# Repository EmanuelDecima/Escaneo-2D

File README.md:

# Escaneo-2D
Este proyecto consiste en un sistema de escaneo rotativo bidimensional diseñado para capturar puntos del contorno de un objeto y representar digitalmente una aproximación de su perímetro

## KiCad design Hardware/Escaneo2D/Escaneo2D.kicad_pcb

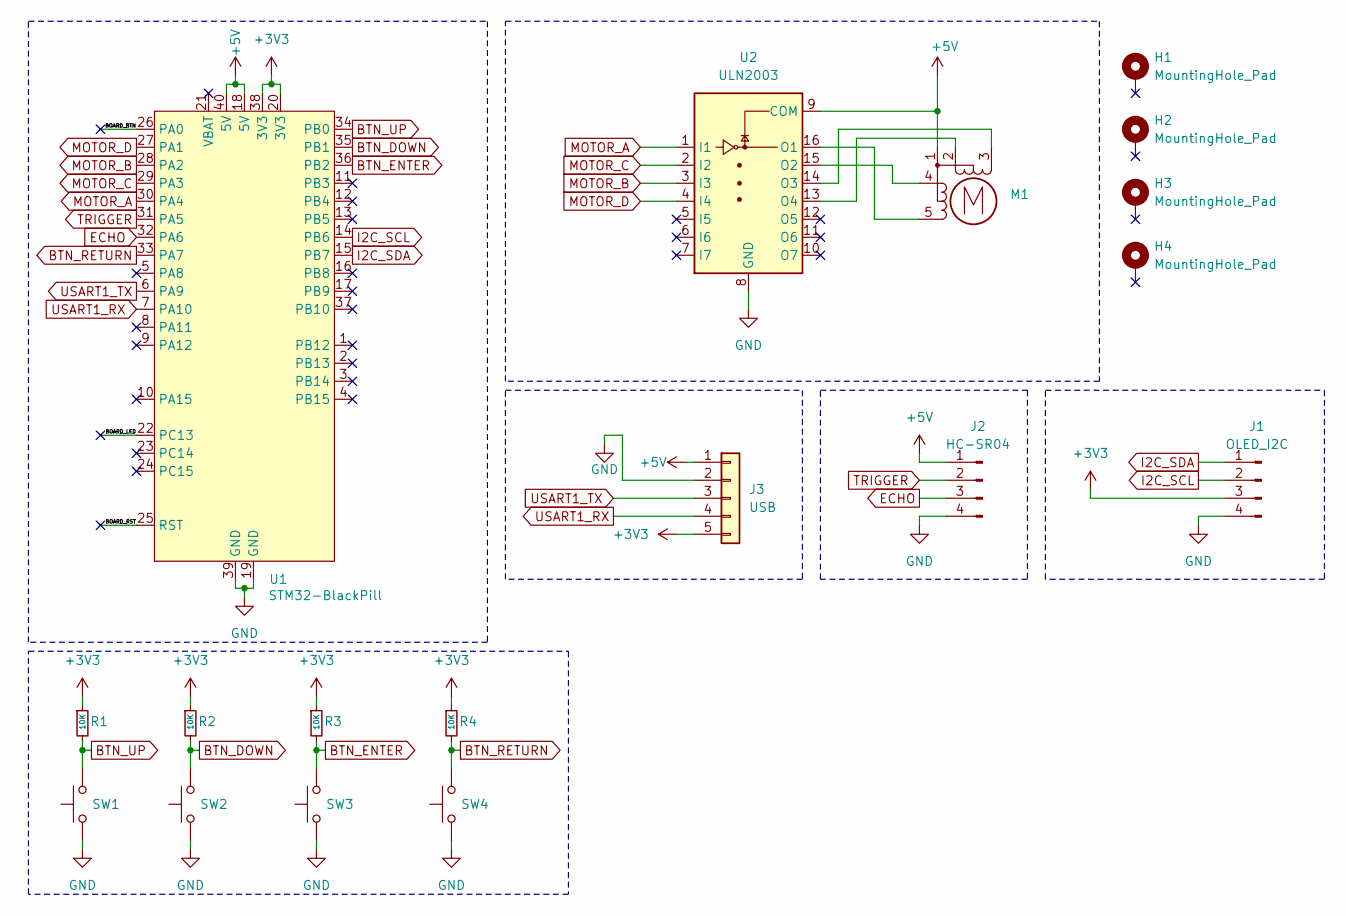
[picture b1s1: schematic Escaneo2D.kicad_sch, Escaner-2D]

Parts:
H1, H2, H3, H4: MountingHole_Pad; MountingHole_2.2mm_M2_DIN965_Pad
J1: OLED_I2C; PinSocket_1x04_P2.54mm_Vertical
J2: HC-SR04; PinSocket_1x04_P2.54mm_Vertical
J3: USB; PinSocket_1x05_P2.54mm_Vertical
M1: Stepper_Motor_unipolar_5pin; JST_EH_B5B-EH-A_1x05_P2.50mm_Vertical
R1, R2, R3, R4: 10K; R_Axial_DIN0207_L6.3mm_D2.5mm_P7.62mm_Horizontal
SW1, SW2, SW3, SW4: SW_Push; SW_PUSH-12mm
U1: STM32-BlackPill; STM32BlackPill
U2: ULN2003; DIP-16_W7.62mm_LongPads

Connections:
+3V3: J1.3, J3.5, R1.1, R2.1, R3.1, R4.1, U1.20 (3V3), U1.38 (3V3)
+5V: J2.1, J3.1, M1.1, U1.18 (5V), U1.40 (5V), U2.9 (COM)
/BOARD_BTN: U1.26 (PA0)
/BOARD_LED: U1.22 (PC13)
/BOARD_RST: U1.25 (RST)
BTN_DOWN: R2.2, SW2.2, U1.35 (PB1)
BTN_ENTER: R3.2, SW3.2, U1.36 (PB2)
BTN_RETURN: R4.2, SW4.2, U1.33 (PA7)
BTN_UP: R1.2, SW1.2, U1.34 (PB0)
ECHO: J2.3, U1.32 (PA6)
GND: J1.4, J2.4, J3.2, SW1.1, SW2.1, SW3.1, SW4.1, U1.19 (GND), U1.39 (GND), U2.8 (GND)
I2C_SCL: J1.2, U1.14 (PB6)
I2C_SDA: J1.1, U1.15 (PB7)
MOTOR_A: U1.30 (PA4), U2.1 (I1)
MOTOR_B: U1.28 (PA2), U2.3 (I3)
MOTOR_C: U1.29 (PA3), U2.2 (I2)
MOTOR_D: U1.27 (PA1), U2.4 (I4)
unnamed: M1.3 (-), U2.14 (O3)
unnamed: M1.5, U2.16 (O1)
unnamed: M1.4, U2.15 (O2)
unnamed: M1.2, U2.13 (O4)
TRIGGER: J2.2, U1.31 (PA5)
USART1_RX: J3.4, U1.7 (PA10)
USART1_TX: J3.3, U1.6 (PA9)

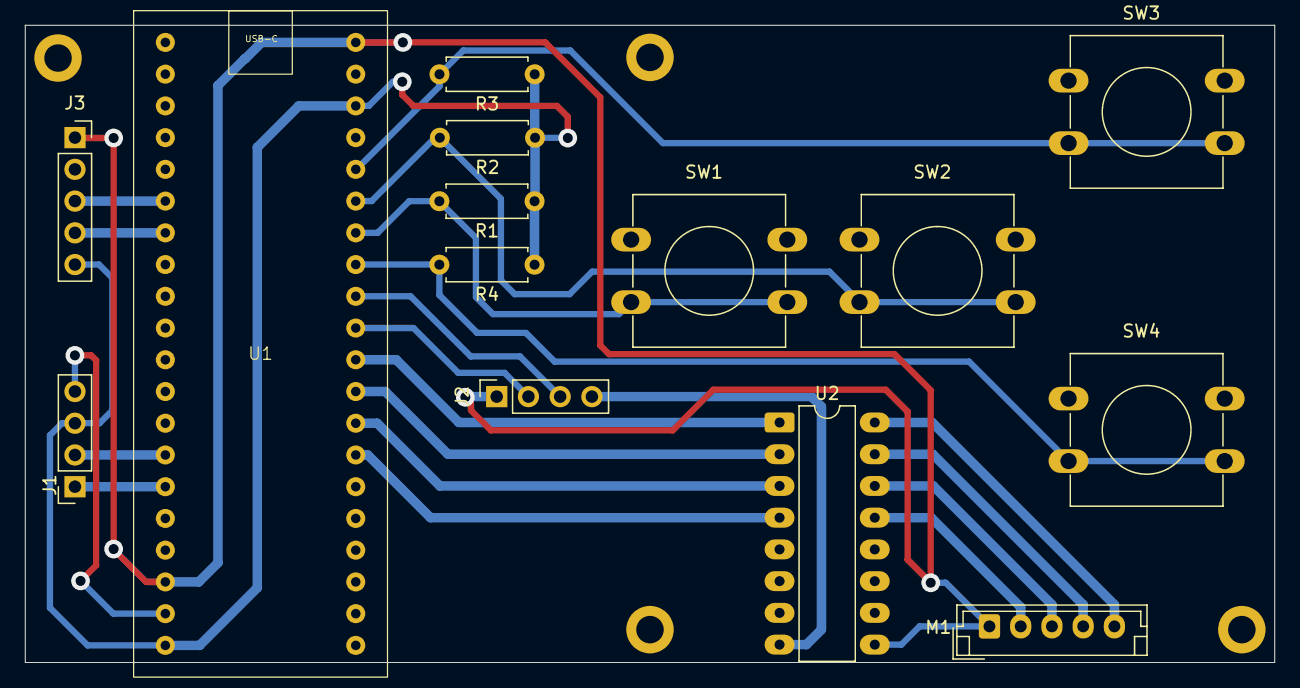
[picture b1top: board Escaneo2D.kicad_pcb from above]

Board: 2 copper layers, 100.0 x 51.0 mm, 18 parts (0 on the bottom side), 21 nets.

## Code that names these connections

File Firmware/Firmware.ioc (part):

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Mcu.Name=STM32F401C(B-C)Ux
Mcu.Package=UFQFPN48
Mcu.UserName=STM32F401CCUx
PA1.GPIOParameters=GPIO_Label
PA1.GPIO_Label=MOTOR_D
PA1.Signal=GPIO_Output
PA10.Mode=Asynchronous
PA10.Signal=USART1_RX
PA13.Mode=Serial_Wire
PA13.Signal=SYS_JTMS-SWDIO
PA14.Mode=Serial_Wire
PA14.Signal=SYS_JTCK-SWCLK
PA2.GPIOParameters=GPIO_Label
PA2.GPIO_Label=MOTOR_B
PA2.Signal=GPIO_Output
PA3.GPIOParameters=GPIO_Label
PA3.GPIO_Label=MOTOR_C
PA3.Signal=GPIO_Output
PA4.GPIOParameters=GPIO_Label
PA4.GPIO_Label=MOTOR_A
PA4.Signal=GPIO_Output
PA5.GPIOParameters=GPIO_Label
PA5.GPIO_Label=TRIGGER
PA5.Signal=GPIO_Output
PA6.Signal=S_TIM3_CH1
PA7.GPIOParameters=GPIO_Label
PA7.GPIO_Label=BTN_RETURN
PA7.Signal=GPXTI7
PA9.Mode=Asynchronous
PA9.Signal=USART1_TX
PB0.GPIOParameters=GPIO_Label
PB0.GPIO_Label=BTN_UP
PB0.Signal=GPXTI0
PB1.GPIOParameters=GPIO_Label
PB1.GPIO_Label=BTN_DOWN
PB1.Signal=GPXTI1
PB2.GPIOParameters=GPIO_Label
PB2.GPIO_Label=BTN_ENTER
PB2.Signal=GPXTI2
PB6.Mode=I2C
PB6.Signal=I2C1_SCL
PB7.Mode=I2C
PB7.Signal=I2C1_SDA
PC14-OSC32_IN.Mode=LSE-External-Oscillator
PC14-OSC32_IN.Signal=RCC_OSC32_IN
PC15-OSC32_OUT.Mode=LSE-External-Oscillator
PC15-OSC32_OUT.Signal=RCC_OSC32_OUT
PH0\ -\ OSC_IN.Mode=HSE-External-Oscillator
PH0\ -\ OSC_IN.Signal=RCC_OSC_IN
PH1\ -\ OSC_OUT.Mode=HSE-External-Oscillator
PH1\ -\ OSC_OUT.Signal=RCC_OSC_OUT
RCC.HSE_VALUE=25000000
RCC.SYSCLKFreq_VALUE=16000000
board=custom

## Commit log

2025-09-22 Proyecto iniciado en STM32CubeIDE
2025-09-23 Librerias Testeadas y Maquina de estados funcionando correctamente
2025-09-24 MEF funcional (falta comunicacion UART) y MotorPAP funciona
2025-09-25 PCB Diseñada
2025-09-26 PCB Terminada
2025-09-27 agrego librerias hcsr04 y uart
2025-09-27 Cambio de Pinout y Refactorizacion del codigo
